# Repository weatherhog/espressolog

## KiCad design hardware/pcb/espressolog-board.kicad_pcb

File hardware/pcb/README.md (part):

# espressolog board — PCB (sense + drive)

One board to replace the hand-wired perfboard. The devkit sits in sockets,
both the sense dividers and the drive side are on it, and **the T-pieces are
on it too** (decided 2026-11-24). The perfboard keeps logging on the machine
until this board has passed its bench test.

**The source is `gen_schematic.py`, not the drawing.** The schematic is
label-based: every pin has a short stub and a net label, so the connectivity is
exactly the `part(...)` calls in the script. Edit the script and regenerate.
Do not edit the `.kicad_sch` by hand.

```bash
python3 gen_schematic.py --check
```

That writes `espressolog-board.kicad_sch` and the symbol library, then runs ERC
and exports the netlist from KiCad. It fails if any net differs from the script.
That proves the drawing matches the script. **It does not prove the script
matches the docs**: that needs a review against `docs/board-and-perfboard.md`
("Sense-side layout", "Drive-side layout") and `firmware/src/main.cpp`.

Needs KiCad 10 (`brew install --cask kicad`). Outputs go to `build/`, which is
not committed.

## The T-pieces are on the board

Each machine connector has two headers on the top edge:
- **IN** (J5, J4, J3, J2): side-entry, opening at the edge. The machine's
  **original harness plug** mates here.
- **OUT** (J25, J24, J23, J22): vertical, right behind its IN. A
  ready-made XH cable runs from here to the machine board's own header.
  **It must map pin 1 to pin 1.** Don't buy by the direction word: in
  同向 / 反向 ("same" / "reverse") listings, the pin-1-to-pin-1 cable is
  probably the one whose latches face OPPOSITE sides when laid flat. Two
  identical plugs on an uncrossed cable, both latches up, are mirrored
  (final review S1). Metering step 1 below decides, whatever the listing
  says.

**IN pin k is joined to OUT pin k by one straight track, for every line.** A
plug mates any XH header of its size the same way, so the machine sees its
own harness, conductor for conductor. The taps branch off the OUT pins. IN
and OUT of one connector are electrically interchangeable.

**A harness plug in the WRONG connector's header: closed for the harness
plugs, 2026-11-25.** The four have different pin counts (2, 3, 4, 5), and in
the paper test a smaller harness plug did not seat in a larger header. The
OUT cables are new parts and were not tried; the pairs are named on the silk
beside both headers.

**Operating consequence: the machine's switches, display and flowmeter all
run through this board. Without it, the machine runs only with the original
plugs back on its own headers.**

**The NTC plug stays on the machine's own J3 header for now** (pre-order
review S2). The J3 pass-through exists on the board, but an open or
resistive joint in it reads as a cold boiler, and with the tap unfitted it
delivers nothing. J3 is a 2-pin XH (confirmed 2026-11-24). The one planned
use before the tap is fitted is the measuring run in "The J3 NTC tap" below.
Before that run:
- find out, machine cold, what the machine does when J3 is pulled;
- meter the J3 rows as in "Before first fit" (pin 1 – pin 2 open, each pin
  open to TP1).

**The taps load the machine even when the ESP32 is off, and they cannot be
unplugged separately** (S12). With the devkit fitted but unpowered, its GPIO
protection diodes clamp the tap nodes, and the J5 bus high level is
calculated to drop from 4.20 V to about 3.5–3.8 V. That is at the floor the
display needs (`docs/phase-0-status.md`). **Measure it once**: machine on,
USB out, J25 pin 2 and pin 3 against TP1. Record the result here. If the
display misreads in that state, the cure is to pull the devkit or go back to
the original plugs.

**Pin map, by JST pin number** (pad 1 is the right-hand pin; the silk at the
top edge names each column, which is the same pin on IN and OUT).
**For J5 this is NOT `CLAUDE.md`'s numbering:** there, and in the display-bus
doc, pin 1 is `VSS` (the spoked pad) and pin 4 is `Disp-P4`. On this board
pad 1 is `Disp-P4` and pad 4 is `VSS`. Never clip a ground to "J5 pin 1" of
this board; ground is TP1.

| Conn | Pin 1 | Pin 2 | Pin 3 | Pin 4 | Pin 5 | Source |
|---|---|---|---|---|---|---|
| J5 / J25 | `Disp-P4` (P4) | `ESD4` clock (CK) | `ESD1` data (DA) | `VSS` (0V) | | pad 1 read off the plug (2026-11-24); the rest positional, `docs/machine-display-bus.md` |
| J4 / J24 | `#` | **`+`** (middle, green) | `T` | | | read off the machine-side plug, Lucas, 2026-11-24 (`J4_T_PIN = "3"` in `gen_schematic.py`) |
| J3 / J23 | NTC P1 | NTC P2 | | | | 109 kΩ between the two (2026-11-24); which is the divider node is unmeasured; the tap is DNP |
| J2 / J22 | pos 1 +5 V | Steam | 2Cup | 1Cup | Water | pad 1 read off the plug (2026-11-24); the rest positional (`CLAUDE.md`, J2 table) |

- **J4 `+` and J5 `Disp-P4` cross the board as isolated pass-through traces.**
  They have no pad but their own header pins, no test point, no via, no pour
  nearby, and keep 2 mm from everything of ours. Their own header's
  neighbouring pins sit at the machine's 2.5 mm pitch (0.8 mm gap, as in the
  machine's harness), and the pass-through tracks of those neighbours run
  1.45 mm from their pads (for `+` that includes J4's own ground, `T`).
  Nothing connects to them (the J4 `+` rule in `CLAUDE.md`).
- **The machine's ground (J5 `VSS`, J4 `T`) is our ground.** It passes
  straight through IN→OUT. J4 `T` ties to the devkit GND (J12 pin 1) by a
  hand-laid track, and J5 `VSS` joins that track through a via. The J2
  dividers' only reference is this ground.

## What the board carries

| Part | Note |
|---|---|
| J11 / J12 | devkit signal column (A) and opposite column (K), 1×22 female headers 25.4 mm apart, pin 1 (3V3) at the top. **Nothing on 5Vin.** Outline on the silkscreen |
| J2–J5 / J22–J25 | IN / OUT, above |
| R1–R16, C1–C3 | sense series legs and shunts. C1–C3 are DNP footprints for the candidate shunt caps (470 pF / 470 pF / 10 nF; **never 10 nF on ESD1/ESD4**) |
| R60–R68, C20–C22, U8 | **J3 NTC tap, ALL DNP** until J3 is measured (section "The J3 NTC tap" below). The machine's PID regulates on this NTC, so any load shifts the brew temperature, and a fault that reads cold keeps the heater on. Wash the flux off: leakage matters at 9.4 MΩ |
| U1, U2 | drive '221s, in sockets. **Crossed (pre-order review S1): U1 drives photoMOS 1 of each chain (U4, U6), U2 drives photoMOS 2 of each (U5, U7)**, so a fault in one package closes at most one device per chain. The perfboard doc has U1 = 1Cup, U2 = 2Cup. GPIOs, net names and firmware are the same either way |
| U3 | the PROPOSED gate '221. **Socket fitted, chip out, and R36 out with it** (R36 is marked DNP) |
| U4–U7 | AQY212EH in a DIP-8 footprint, with the chip at the pin-1 end of an uncut DIL08PZ (or soldered straight in). Pads 3–6 are not connected |
| Q1–Q4 + R40–R51 | LED-driver cells: 330 Ω, BC547B, 100 K, 8.2 K |
| JP1 (a1), JP2 (a2) | in series with the photoMOS outputs. **OPEN through Phase 0** (invariant 1) |
| JP3 (b) | LED supply. **OPEN until the bench test** |
| JP4 | selftest GPIO8–GPIO6. **Never fitted in service** |
| TP1 / TP2 | GND and 3V3 test loops for the scope and analyser |

**GPIO changes against the perfboard:** U1 pin 13's readback (1Cup
photoMOS 1) is on **GPIO11** (signal column position 17), and **GPIO1**
(opposite column position 4) is the NTC's ADC input (`30beb28`).

## Not settled. Check before ordering

- **J4: `+` is the MIDDLE pin; which outer pin is `T` is `J4_T_PIN`.** The
  first T-piece commit (`ee2795e`) took `docs/phase-0-status.md`'s "`T`
  (middle)" at its word and tied the machine's `+` to our GND. That doc was
  wrong, and Lucas read the plug. `T` is tied to our GND, so its side came
  from the plug, not a guess. `J4_T_PIN` and `J4_FLOW_PIN` are constants now
  and finish.py checks the pads against them: changing one stops the build
  until R3's position and the check are changed with it. That is the point.
- **Plug orientation: CONFIRMED 2026-11-24 for J4, J5 and J2.** Lucas read
  each machine-side plug from its wire end with the latches up (the latch
  faces up on a side-entry header, also confirmed), which mirrors left and
  right against the board frame:
  - J4: `+` (green) in the middle, `#` (black) on pad 1, `T` (yellow) on
    pad 3;
  - J5: `Disp-P4` on pad 1;
  - J2: the +5 V common on pad 1.

  The pre-power check below still confirms all three on the built board.
- **Capacitor lead pitch: checked in the paper test (2026-11-25).** The
  footprints are 5.0 mm. The 1 µF MKT and the 470 pF fit; the 100 nF discs
  in hand are narrower and get their legs splayed. The 10 nF was not tried.
- **BC547 footprint:** `TO-92_Inline_Wide`, with legs 2.54 mm apart like the
  perfboard's (the standard 1.27 mm one puts the collector–base pair close
  together). Pad 1 is C, and the review checked this against KiCad's stock
  BC547. A 2N3904 would go in reversed.
- **One GND net.** The perfboard kept separate drive (K29) and sense (K30)
  ground ties. Signal-column GND (A22, beside 5Vin) is deliberately left
  unused, as on the perfboard.
- **AQY212EH in an uncut DIP-8 footprint** where the board doc says DIP-4
  sockets: same netlist, and a chip pushed in at the wrong end lands on dead pads.
- **Box headroom above the top edge.** The OUT headers are vertical. A plug
  plus its cable bend needs ~20–25 mm above the board.
- **The open design items stay open**: the readback value (1 K proposed), the
  gate RC (470 K candidate), and whether the gate stays. They are on ordinary
  footprints, so values are chosen at soldering time. Dropping the gate is a
  bodge wire, GPIO38 to the arm net, not a solder jumper. The minimum-gap stage
  on U3's spare channel is not designed, so U3 channel 2 is tied off.

## The J3 NTC tap (all DNP, values not final)

J3 is the PID's own temperature sensor, so this is the one tap where a
mistake changes what the machine does to the boiler. Everything here is a
footprint; nothing is fitted until the measurements below exist.

**Measured so far (Lucas, 2026-11-24):** J3 is a 2-pin JST XH, and the
sensor reads **109 kΩ between its two wires**, plug off the machine board,
at what was presumably room temperature. That
fits a 100 kΩ NTC (B ≈ 3950 gives 109 kΩ at 23 °C), which would be roughly
6–9 kΩ at 95 °C. The B value, which pin is the divider node, the pull-up
and the node voltage are **not measured**.

**The circuit:**

| Part | Value | What it does |
|---|---|---|
| R60 **or** R61 | 4.7 MΩ, **fit ONE** | from the divider-node pin (R60 = pin 1, R61 = pin 2) to `NTC_MID`. Both fitted put 9.4 MΩ across the NTC |
| R64 | 4.7 MΩ | `NTC_MID` → `NTC_TAP`. Two parts in series, so one bridged or failed part still leaves 4.7 MΩ on the line |
| R62 | open | shunt to GND, only if the node turns out to sit above ~3 V (5 V referenced) |
| C20 | 10 nF | at the op-amp input |
| U8 half A | MCP6002 | unity follower (CMOS input, ~1 pA) |
| U8 half B, R66, R67 | Rf, Rg | follows half A. **Wire link in R66, R67 empty = unity** (the parked default). R66/R67 fitted = gain 1 + R66/R67, for a node that sits low when hot. **Whenever U8 is fitted, R66 is fitted** (link or Rf): without it half B runs open-loop |
| R63 **or** R68 | 1 kΩ, **fit ONE** | R63 from the follower, R68 from the gain stage, into `NTC_ADC` |
| C21, C22 | 100 nF | on `NTC_ADC` (GPIO1, ADC1), and U8's supply |

**What it costs the machine.** In normal running the follower draws
nothing, so the load is leakage only. The worst case is the tap node held
at a rail, and that is also the everyday case of **machine on, logger
off**: U8's input clamps to its dead supply. Then 9.4 MΩ sits across the
node. Against ≤ 9 kΩ at brew temperature that is under 0.1 % of the
reading, about 0.03 °C; against 109 kΩ cold it is ~1.2 %, about 0.3 °C.
**Which way it reads is not known yet:** slightly hot (the direction that
heats less) if the NTC is the leg to ground, slightly cold by the same
amount if it is the leg to the supply. Step 1 below settles it.

**Still to measure, and none of it needs a hand-built T-piece:**
1. **Now, machine off and unplugged:** each pin of the machine board's J3
   header to ground (J5's spoked pad), in Ω. One pin near 0 Ω means that pin
   is ground and the other is the node. (Back-probing J4's header gave no
   reading before; if J3 does the same, skip it, step 2 answers it too.)
2. **With this board, tap unfitted** (after the two checks under "The NTC
   plug stays on the machine" above): J3 through IN → OUT like the other
   three, **with the J5 or J4 OUT cable on the machine too** (TP1 is only
   the machine's ground through one of those). The board is the T-piece.
   Meter J23 pin 1 and pin 2 against TP1 in
   DC volts, cold and at setpoint, and note whether the reading is steady (a
   pulsed excitation would not be). A 10 MΩ meter loads the node as much as
   the tap will.

Those readings choose R60 or R61, whether R62 is needed, and the gain
(largest that keeps the hot-end voltage under ~2.5 V at GPIO1). **Running
J3 through the board is itself the risk this section is about**: an open
pass-through reads cold and the heater stays on. Seat both plugs fully and
watch the display on the first heat-up.

Firmware reads nothing on GPIO1 yet. When it does, it stores raw
millivolts (invariant 3) and the conversion lives in analysis.

## Before first fit: meter it

Board unpowered, devkit out, DNP parts unfitted, the NTC plug left on the
machine.

0. **The jumpers are open.** Each of JP1, JP2, JP3 and JP4 reads open across
   its two posts. J22 pin 1 reads open to U4 pad 8 and to U6 pad 8. The posts
   are 0.84 mm apart and hand-soldered, and a bridged JP1 or JP2 is invisible
   from the connectors. Invariant 1 rests on this.

1. **Each OUT cable, on this board.** Plug its two ends into that
   connector's own IN and OUT headers (no harness, no machine).
   - **Correct cable:** pin 1 ↔ pin 1. Each line only loops back to itself,
     so no two different pins are joined.
   - **Mirrored cable:** pin k ↔ pin n+1−k, so pin 1 is shorted to pin n.

   No cavity numbering is needed. Meter on the IN header's solder side:
   - J5: pin 1 – pin 4 must read open (mirrored: `Disp-P4` on GND), and
     pin 2 – pin 3 must read ~49 kΩ (mirrored: ~0);
   - J4: pin 1 – pin 3 must read ~320 kΩ (mirrored: `#` on GND, the `E01`
     class);
   - J3: pin 1 – pin 2 must read open;
   - J2: pin 1 – pin 5 must read open, and pin 2 – pin 4 ~740 kΩ.

   **Any ~0 Ω reading means a mirrored cable, which must not be used.**

   This step finds a mirrored cable and nothing else: an unseated cable or a
   broken conductor reads the same as a good one. So, **for every conductor**:
   one end in the OUT header, probe each contact of the free plug to the
   same pin of the IN header, ~0 Ω.
2. **Board pass-through.** IN pin k reads ~0 Ω to OUT pin k, and **not
   ~0 Ω** to any other pin of either header. The readings between different
   pins are the board's own dividers, not opens:
   - J5: pin 2–3 ≈ 49 kΩ, pin 2 or 3 to pin 4 ≈ 24.6 kΩ, pin 1 open to all;
   - J4: pin 1–3 ≈ 320 kΩ, pin 2 open to all;
   - J2: any two of pins 2–5 ≈ 740 kΩ, pin 1 open to all;
   - J3: open.

   A ~0 Ω reading is a solder bridge.
3. **The isolated lines.** J24 pin 2 (`+`, the middle one) and J25 pin 1
   (`Disp-P4`) read open to every other pin, to TP1 (GND) and to TP2 (3V3).
   J23 pins 1 and 2 read open to everything.
4. **Ground.** J25 pin 4 and the J24 `T` pin read ~0 Ω to TP1, and **J24
   pin 2 does NOT** (that reading is the `ee2795e` short). No J2 pin reads
   ~0 to TP1.
5. **Taps by value**, header pin to devkit socket position:
   - 8.2 kΩ: J25 pin 3 → A5 and J25 pin 2 → A4;
   - 100 kΩ: the J24 `#` pin → A6;
   - 150 kΩ: J22 pins 5, 4, 3, 2 → A10, A7, A8, A9 (the 100 K and 150 K bags
     look alike).
   - Then the shunts, socket position to TP1: A4 and A5 16.4 kΩ, A6–A10
     220 kΩ.
6. **At the machine**, machine off and unplugged from the mains, OUT cables
   to the machine board, harness plugs NOT on the IN headers:
   - TP1 reads ~0 Ω to J5's spoked pad (`VSS`) and to J4's `T`;
   - J24 pin 2 reads ~0 Ω to the machine's J4 `+`, and **not ~0 Ω to TP1**.
     It is never "open" there: the machine's own path `+` → 10 k → `#` →
     147 k → `T` (with our 320 k beside it) reads about 110 kΩ, and the
     unpowered 5 V rail can pull that lower. The value to expect is the
     `+`–`T` reading taken on the machine's own J4 plug (below); a reading
     near **10 kΩ** points at a mirrored J4 cable, and anything under
     ~1 kΩ, down to ~0 Ω, means `+` is on or near ground: stop either way;
   - the J24 `#` pin reads ~0 Ω to `#`;
   - J25 pin 1 reads ~0 Ω to J5's square pad (`Disp-P4`);
   - J22 pin 1 reads ~0 Ω to the machine's J2 common, the pin in every
     lever's continuity pair.

   This confirms the J5, J4 and J2 orientation on the real machine.

   **If the machine board's pins can't be probed** (back-probing J4 gave no
   reading before), there is a J4 check that needs no access to them, derived
   from the 2026-10-04 readings and not yet tried in this form: with the J24
   cable on the unpowered machine and no harness plug, **J24 pin 1 – pin 2
   reads ≈ 10 kΩ** (the machine's pull-up from `#` to `+`), and TP1 – J24
   pin 2 does not. With a mirrored J4 cable both read ≈ 10 kΩ (with J5's
   cable on, `#` is then on `T` through our ground).
   **This only discriminates if the machine's unpowered 5 V rail reads well
   above 10 kΩ, and nobody has measured it.** Meter `+` to `T` once on the
   machine's own J4 plug (machine off, no board attached) before relying on
   it. If that reads near 10 kΩ the two readings look alike and this check
   says nothing.
7. Only then do the harness plugs go on the IN headers (not the NTC's).

**`selftest`:** "unplug J4 first" now means the **J24 OUT cable**. Pulling
only the harness plug leaves GPIO8 on the machine's `#` node through 100 K.

## Building the board

Placement, routing and finishing are scripts too. Each runs with KiCad's
Python (`KPY=/Applications/KiCad/KiCad.app/Contents/Frameworks/Python.framework/Versions/3.9/bin/python3`):

```bash
python3 gen_schematic.py --check   # schematic, ERC, netlist round-trip
$KPY gen_pcb.py                    # placement + the machine nets as locked tracks
$KPY route.py                      # Freerouting the rest, headless (Java 21+, jar in ~/.local/share/freerouting)
$KPY route.py --keep               # second pass: keeps the routes, completes what is still open
$KPY finish.py                     # GND pours (both layers), keep-outs, labels, refs
```

`route.py` can be re-run on a routed board. It strips everything except the
locked tracks in a separate process, then routes. **One pass does not always
finish**: with the tight rules the router can leave a connection open, and
the result varies from run to run. `route.py --keep` routes again on top of
what is there. Repeat it until DRC after `finish.py` shows 0 unconnected.
While routing, the router is kept out of the J5/J4 header block, out of the
corridor between the J3 rows, 1 mm off every board edge, and **out from
under every hand-laid machine track** (a strip on the opposite layer: no
clearance rule sees opposite layers, and one re-route on 2026-11-24 took a
drive net between the J2 rows under all five lever pass-throughs).

**A router run is not reproducible, and it can leave connections open.**
`route.py` prints `open connections: N`; run `route.py --keep` until it is 0,
and if two or three passes do not close it, start again from `gen_pcb.py`
(the next fresh run usually does). The pipeline no longer finishes a bad
board quietly:
- `route.py` deletes `build/routed.kicad_pcb` and the old router session
  before it starts, and stops if Freerouting fails;
- `finish.py` starts from `build/routed.kicad_pcb` and **stops before
  saving** unless: every pad is on the net `gen_schematic.py` gives it; the
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
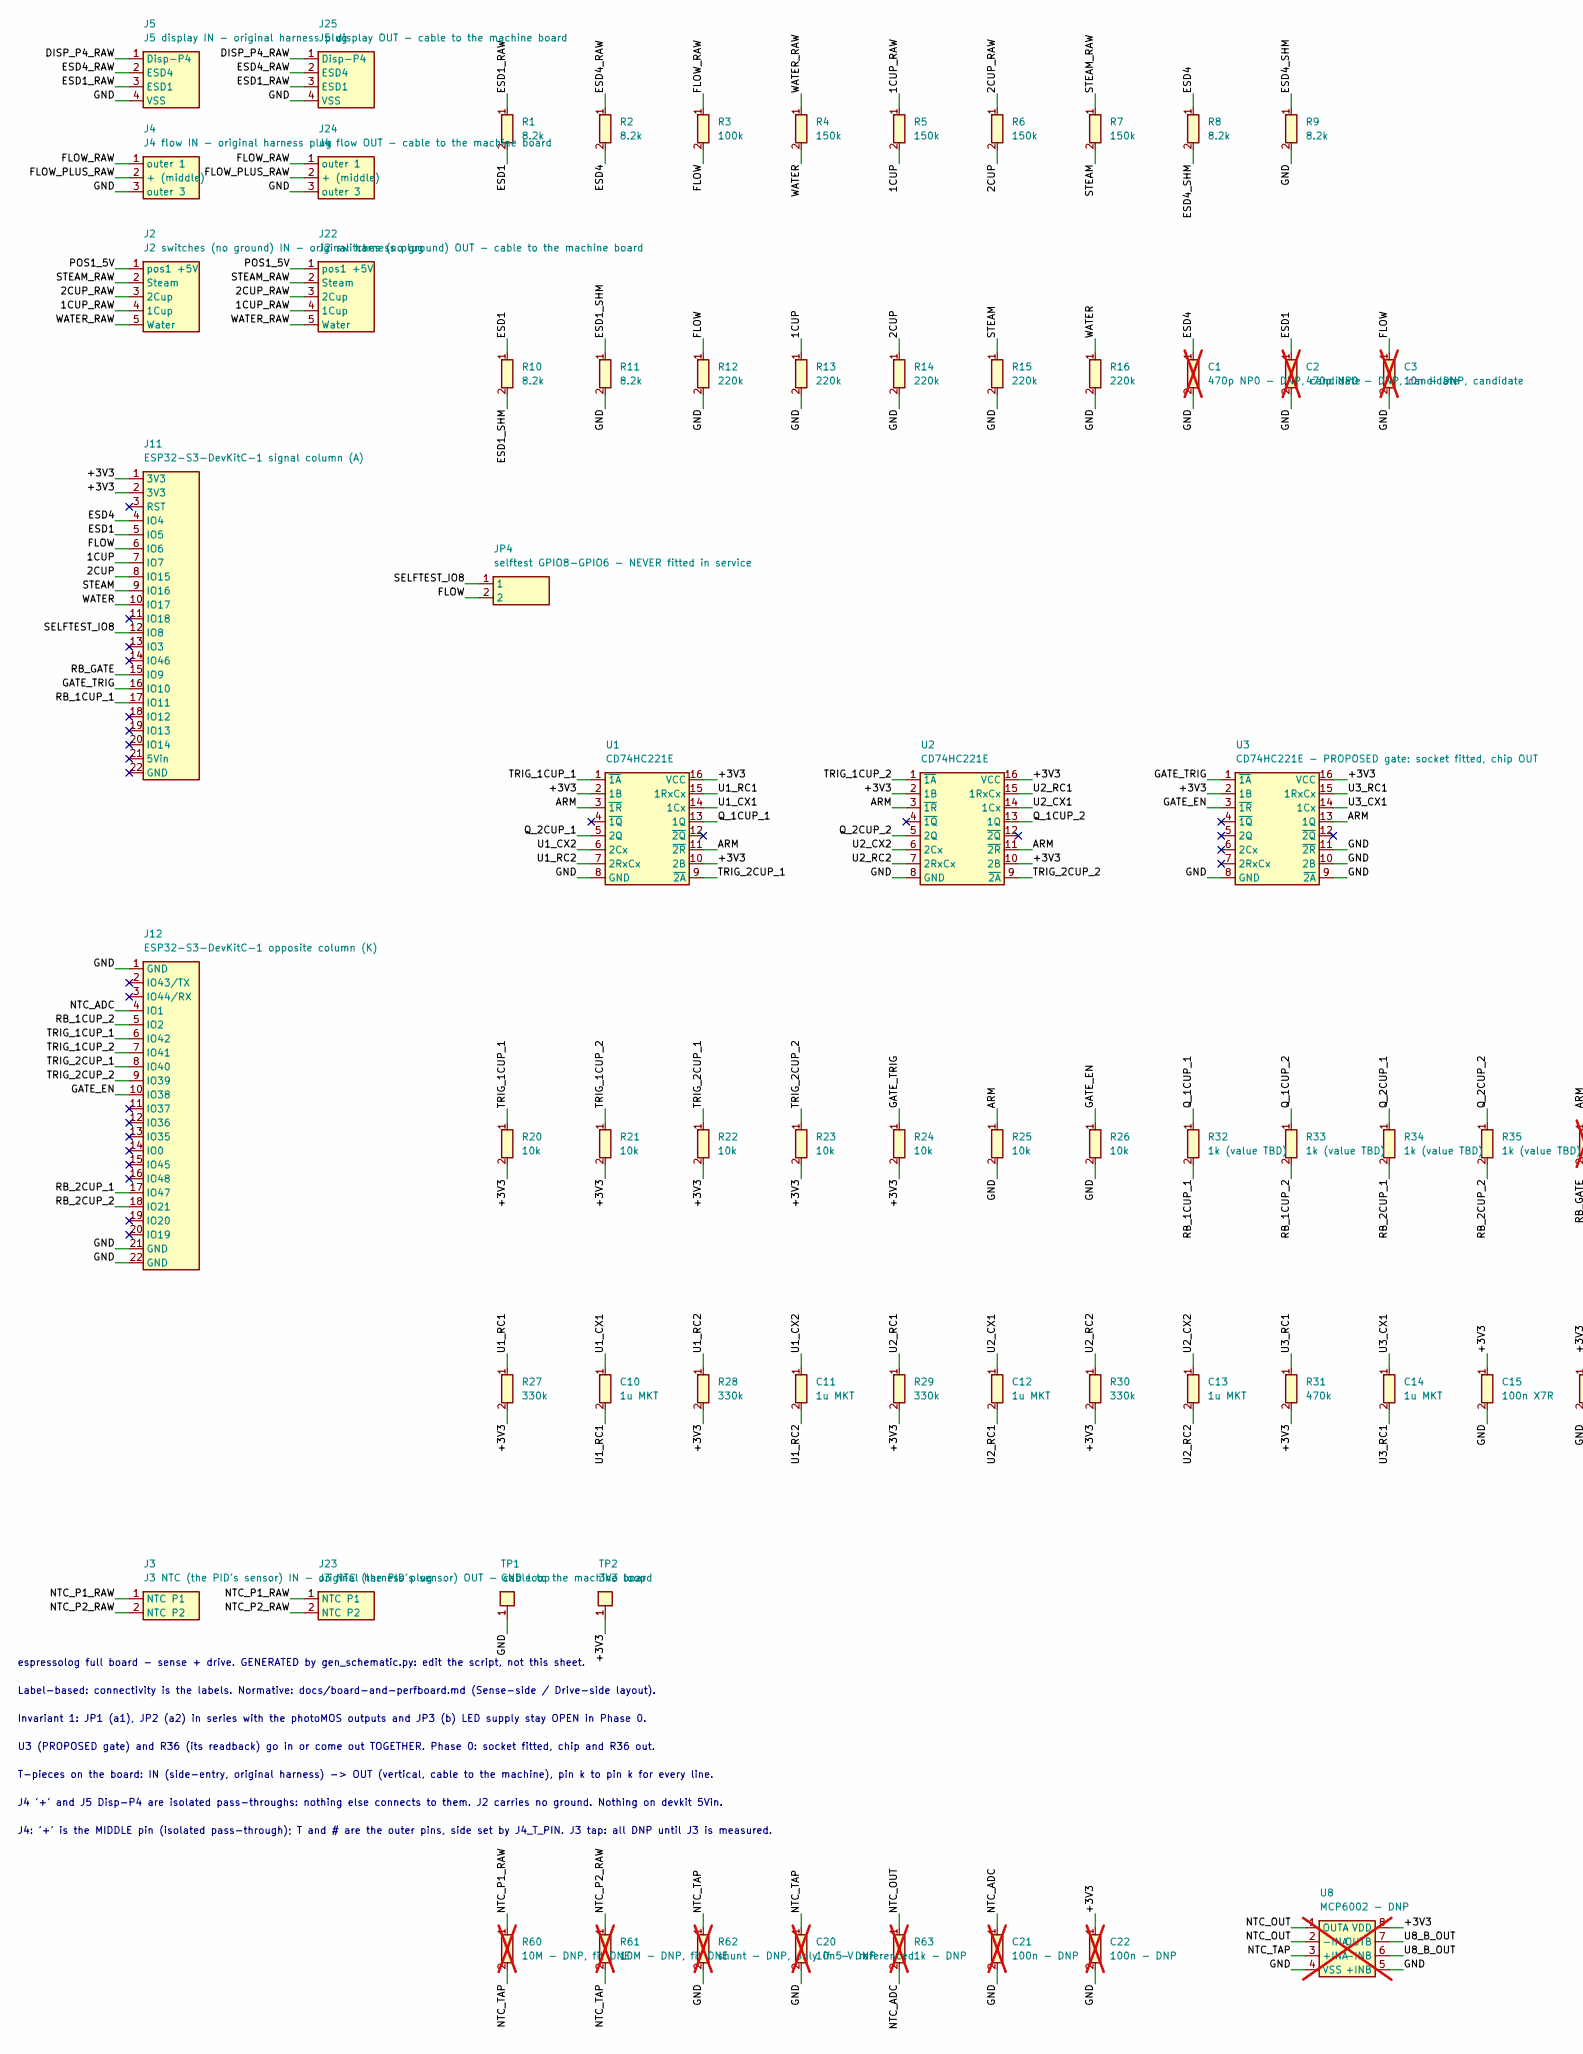
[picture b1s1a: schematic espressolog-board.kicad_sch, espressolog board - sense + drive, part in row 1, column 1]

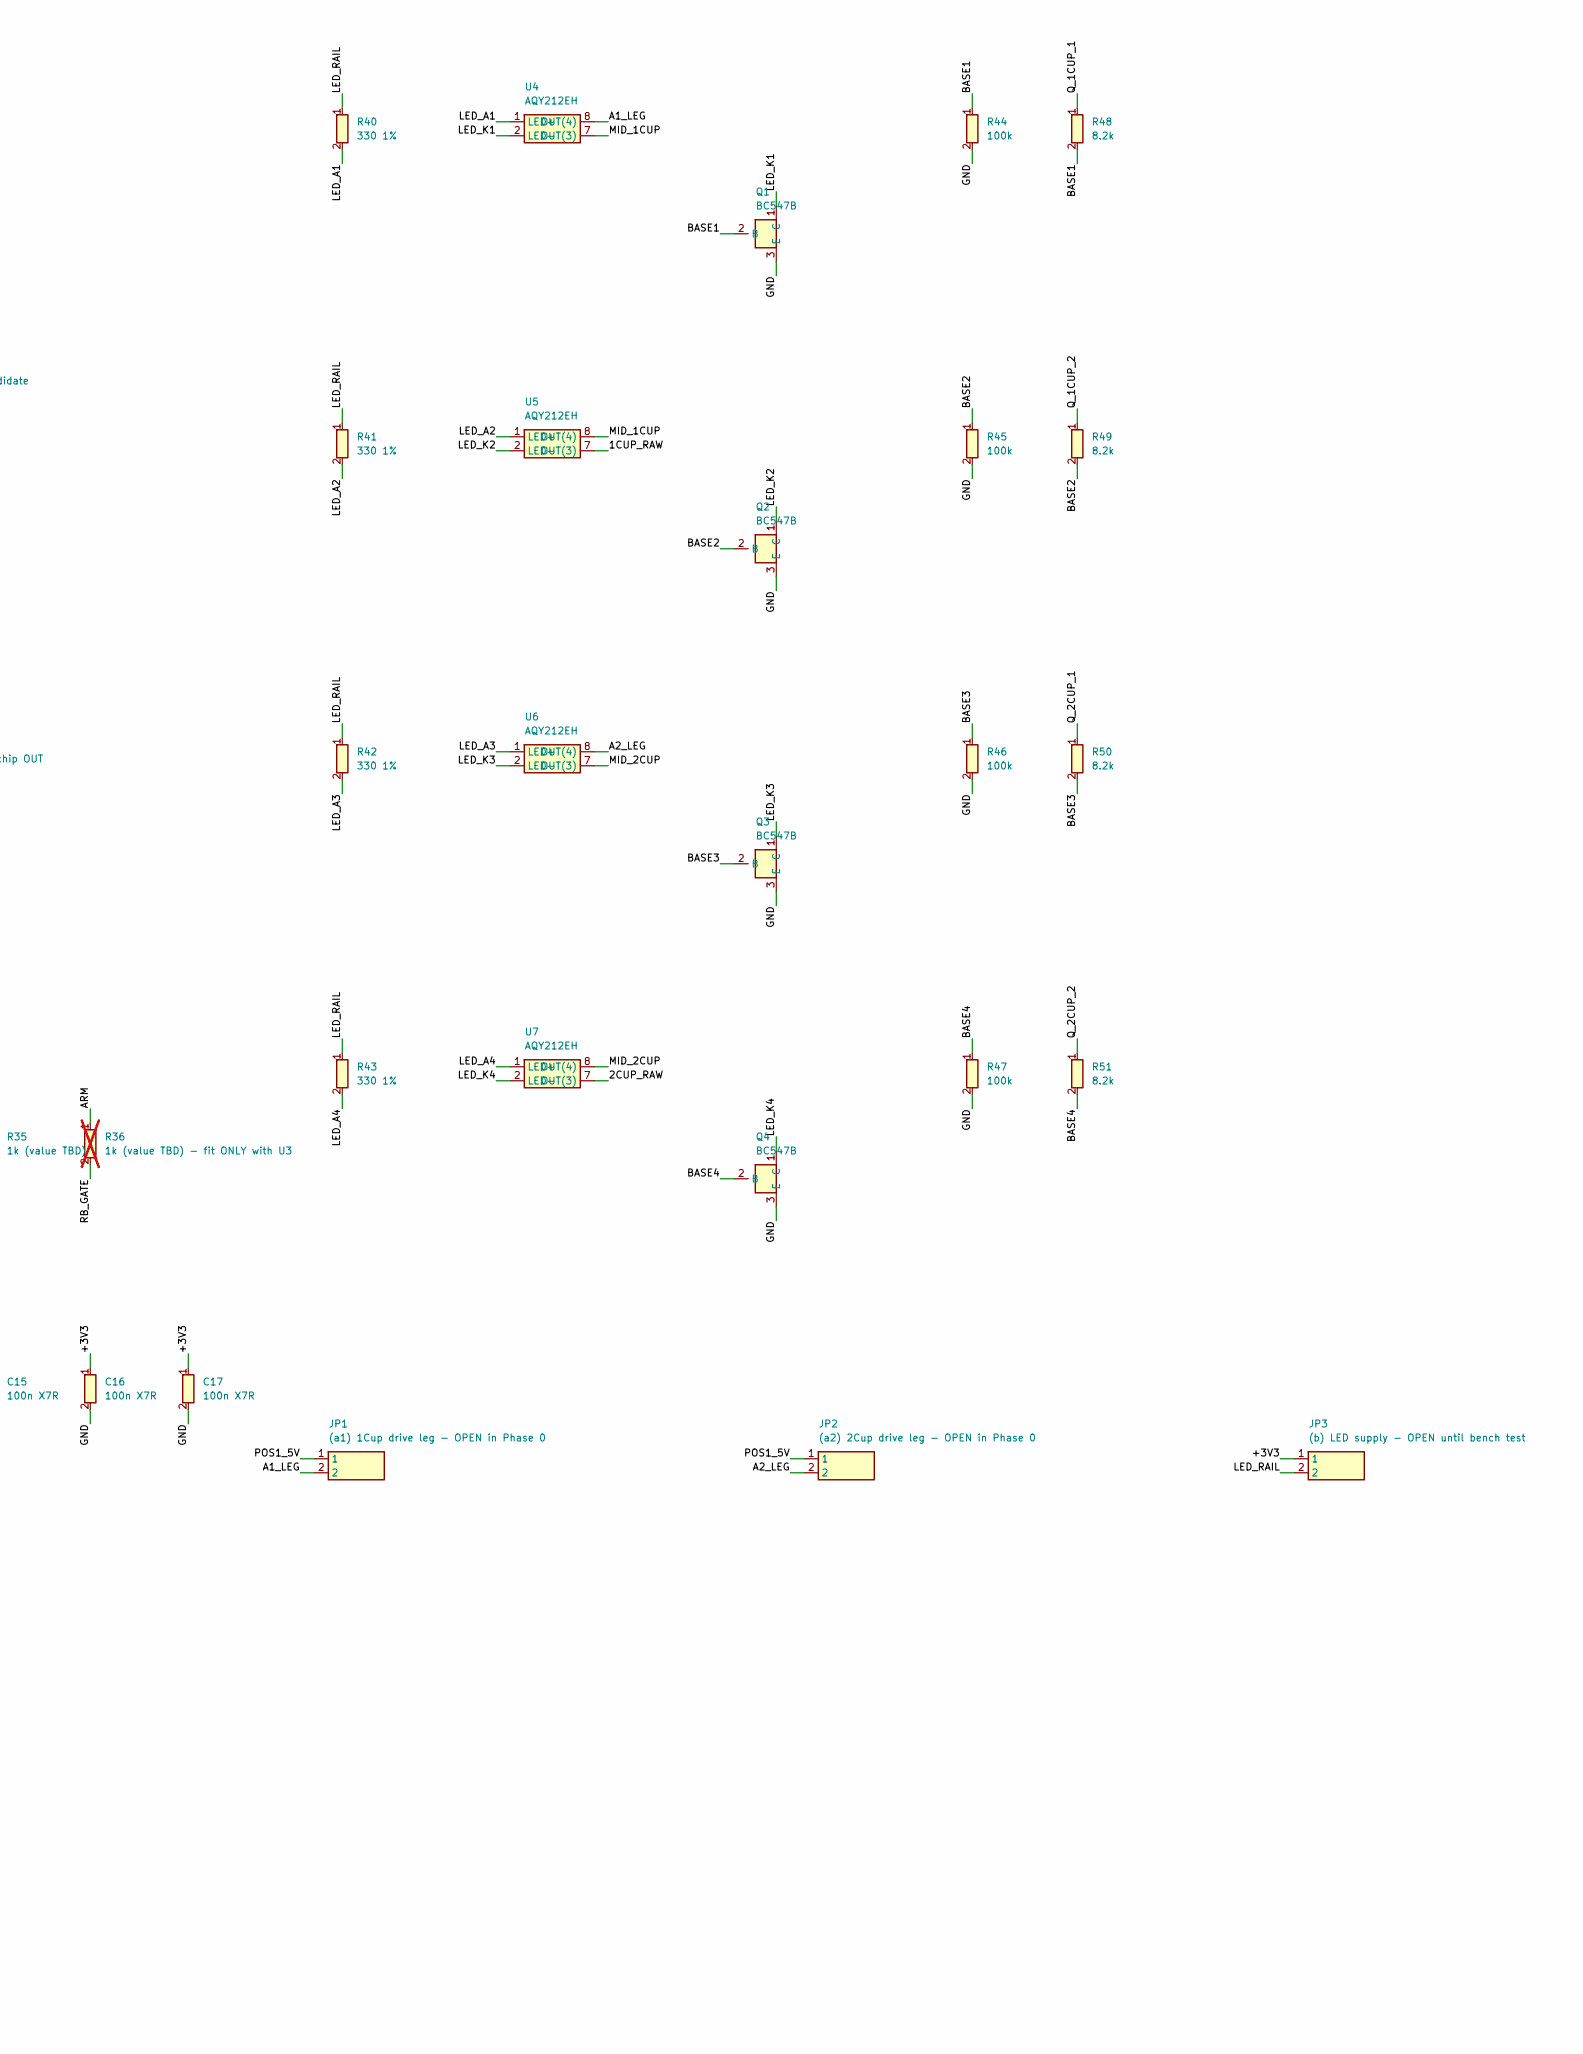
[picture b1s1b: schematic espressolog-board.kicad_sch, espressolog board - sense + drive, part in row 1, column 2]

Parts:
C1, C2: 470p NP0 - DNP, candidate; C_Disc_D5.0mm_W2.5mm_P5.00mm; not fitted
C3: 10n - DNP, candidate; C_Disc_D5.0mm_W2.5mm_P5.00mm; not fitted
C10, C11, C12, C13, C14: 1u MKT; C_Rect_L7.2mm_W5.5mm_P5.00mm_FKS2_FKP2_MKS2_MKP2
C15, C16, C17: 100n X7R; C_Disc_D5.0mm_W2.5mm_P5.00mm
C20: 10n - DNP; C_Disc_D5.0mm_W2.5mm_P5.00mm; not fitted
C21, C22: 100n - DNP; C_Disc_D5.0mm_W2.5mm_P5.00mm; not fitted
J2: J2 switches (no ground) IN - original harness plug; JST_XH_S5B-XH-A_1x05_P2.50mm_Horizontal
J3: J3 NTC (the PID's sensor) IN - original harness p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; JST_XH_S2B-XH-A_1x02_P2.50mm_Horizontal
J4: J4 flow IN - original harness plug; JST_XH_S3B-XH-A_1x03_P2.50mm_Horizontal
J5: J5 display IN - original harness plug; JST_XH_S4B-XH-A_1x04_P2.50mm_Horizontal
J11: ESP32-S3-DevKitC-1 signal column (A); PinSocket_1x22_P2.54mm_Vertical
J12: ESP32-S3-DevKitC-1 opposite column (K); PinSocket_1x22_P2.54mm_Vertical
J22: J2 switches (no ground) OUT - cable to the machin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; JST_XH_B5B-XH-A_1x05_P2.50mm_Vertical
J23: J3 NTC (the PID's sensor) OUT - cable to the mach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; JST_XH_B2B-XH-A_1x02_P2.50mm_Vertical
J24: J4 flow OUT - cable to the machine board; JST_XH_B3B-XH-A_1x03_P2.50mm_Vertical
J25: J5 display OUT - cable to the machine board; JST_XH_B4B-XH-A_1x04_P2.50mm_Vertical
JP1: (a1) 1Cup drive leg - OPEN in Phase 0; PinHeader_1x02_P2.54mm_Vertical
JP2: (a2) 2Cup drive leg - OPEN in Phase 0; PinHeader_1x02_P2.54mm_Vertical
JP3: (b) LED supply - OPEN until bench test; PinHeader_1x02_P2.54mm_Vertical
JP4: selftest GPIO8-GPIO6 - NEVER fitted in service; PinHeader_1x02_P2.54mm_Vertical
Q1, Q2, Q3, Q4: BC547B; TO-92_Inline_Wide
R1, R2, R8, R9, R10, R11: 8.2k; R_Axial_DIN0207_L6.3mm_D2.5mm_P10.16mm_Horizontal
R3: 100k; R_Axial_DIN0207_L6.3mm_D2.5mm_P10.16mm_Horizontal
R4, R5, R6, R7: 150k; R_Axial_DIN0207_L6.3mm_D2.5mm_P7.62mm_Horizontal
R12, R13, R14, R15, R16: 220k; R_Axial_DIN0207_L6.3mm_D2.5mm_P10.16mm_Horizontal
R20, R21, R22, R23, R24, R25, R26: 10k; R_Axial_DIN0207_L6.3mm_D2.5mm_P2.54mm_Vertical
R27, R28, R29, R30: 330k; R_Axial_DIN0207_L6.3mm_D2.5mm_P2.54mm_Vertical
R31: 470k; R_Axial_DIN0207_L6.3mm_D2.5mm_P2.54mm_Vertical
R32, R33, R34, R35: 1k (value TBD); R_Axial_DIN0207_L6.3mm_D2.5mm_P2.54mm_Vertical
R36: 1k (value TBD) - fit ONLY with U3; R_Axial_DIN0207_L6.3mm_D2.5mm_P2.54mm_Vertical; not fitted
R40, R41, R42, R43: 330 1%; R_Axial_DIN0207_L6.3mm_D2.5mm_P2.54mm_Vertical
R44, R45, R46, R47: 100k; R_Axial_DIN0207_L6.3mm_D2.5mm_P2.54mm_Vertical
R48, R49, R50, R51: 8.2k; R_Axial_DIN0207_L6.3mm_D2.5mm_P2.54mm_Vertical
R60, R61: 10M - DNP, fit ONE; R_Axial_DIN0207_L6.3mm_D2.5mm_P5.08mm_Vertical; not fitted
R62: shunt - DNP, only if 5 V referenced; R_Axial_DIN0207_L6.3mm_D2.5mm_P2.54mm_Vertical; not fitted
R63: 1k - DNP; R_Axial_DIN0207_L6.3mm_D2.5mm_P2.54mm_Vertical; not fitted
TP1: GND loop; TestPoint_Loop_D2.50mm_Drill1.0mm
TP2: 3V3 loop; TestPoint_Loop_D2.50mm_Drill1.0mm
U1, U2: CD74HC221E; DIP-16_W7.62mm_Socket
U3: CD74HC221E - PROPOSED gate: socket fitted, chip O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; DIP-16_W7.62mm_Socket
U4, U5, U6, U7: AQY212EH; DIP-8_W7.62mm_Socket
U8: MCP6002 - DNP; DIP-8_W7.62mm; not fitted

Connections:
1CUP: J11.7 (IO7), R5.2, R13.1
1CUP_RAW: J2.4 (1Cup), J22.4 (1Cup), R5.1, U5.7 (OUT(3))
2CUP: J11.8 (IO15), R6.2, R14.1
2CUP_RAW: J2.3 (2Cup), J22.3 (2Cup), R6.1, U7.7 (OUT(3))
+3V3: C15.1, C16.1, C17.1, C22.1, J11.1 (3V3), J11.2 (3V3), JP3.1, R20.2, R21.2, R22.2, R23.2, R24.2, R27.2, R28.2, R29.2, R30.2, R31.2, TP2.1, U1.2 (1B), U1.10 (2B), U1.16 (VCC), U2.2 (1B), U2.10 (2B), U2.16 (VCC), U3.2 (1B), U3.16 (VCC), U8.8 (VDD)
A1_LEG: JP1.2, U4.8 (OUT(4))
A2_LEG: JP2.2, U6.8 (OUT(4))
ARM: R25.1, R36.1, U1.3 (~1R), U1.11 (~2R), U2.3 (~1R), U2.11 (~2R), U3.13 (1Q)
BASE1: Q1.2 (B), R44.1, R48.2
BASE2: Q2.2 (B), R45.1, R49.2
BASE3: Q3.2 (B), R46.1, R50.2
BASE4: Q4.2 (B), R47.1, R51.2
DISP_P4_RAW: J5.1 (Disp-P4), J25.1 (Disp-P4)
ESD1: C2.1, J11.5 (IO5), R1.2, R10.1
ESD1_RAW: J5.3 (ESD1), J25.3 (ESD1), R1.1
ESD1_SHM: R10.2, R11.1
ESD4: C1.1, J11.4 (IO4), R2.2, R8.1
ESD4_RAW: J5.2 (ESD4), J25.2 (ESD4), R2.1
ESD4_SHM: R8.2, R9.1
FLOW: C3.1, J11.6 (IO6), JP4.2, R3.2, R12.1
FLOW_PLUS_RAW: J4.2 (+ (middle)), J24.2 (+ (middle))
FLOW_RAW: J4.1 (outer 1), J24.1 (outer 1), R3.1
GATE_EN: J12.10 (IO38), R26.1, U3.3 (~1R)
GATE_TRIG: J11.16 (IO10), R24.1, U3.1 (~1A)
LED_A1: R40.2, U4.1 (LED+)
LED_A2: R41.2, U5.1 (LED+)
LED_A3: R42.2, U6.1 (LED+)
LED_A4: R43.2, U7.1 (LED+)
LED_K1: Q1.1 (C), U4.2 (LED-)
LED_K2: Q2.1 (C), U5.2 (LED-)
LED_K3: Q3.1 (C), U6.2 (LED-)
LED_K4: Q4.1 (C), U7.2 (LED-)
LED_RAIL: JP3.2, R40.1, R41.1, R42.1, R43.1
MID_1CUP: U4.7 (OUT(3)), U5.8 (OUT(4))
MID_2CUP: U6.7 (OUT(3)), U7.8 (OUT(4))
NTC_ADC: C21.1, J12.4 (IO1), R63.2; also elsewhere on the board
NTC_P1_RAW: J3.1 (NTC P1), J23.1 (NTC P1), R60.1
NTC_P2_RAW: J3.2 (NTC P2), J23.2 (NTC P2), R61.1
POS1_5V: J2.1 (pos1 +5V), J22.1 (pos1 +5V), JP1.1, JP2.1
Q_1CUP_1: R32.1, R48.1, U1.13 (1Q)
Q_1CUP_2: R33.1, R49.1, U2.13 (1Q)
Q_2CUP_1: R34.1, R50.1, U1.5 (2Q)
Q_2CUP_2: R35.1, R51.1, U2.5 (2Q)
RB_1CUP_1: J11.17 (IO11), R32.2
RB_1CUP_2: J12.5 (IO2), R33.2
RB_2CUP_1: J12.17 (IO47), R34.2
RB_2CUP_2: J12.18 (IO21), R35.2
RB_GATE: J11.15 (IO9), R36.2
SELFTEST_IO8: J11.12 (IO8), JP4.1
STEAM: J11.9 (IO16), R7.2, R15.1
STEAM_RAW: J2.2 (Steam), J22.2 (Steam), R7.1
TRIG_1CUP_1: J12.6 (IO42), R20.1, U1.1 (~1A)
TRIG_1CUP_2: J12.7 (IO41), R21.1, U2.1 (~1A)
TRIG_2CUP_1: J12.8 (IO40), R22.1, U1.9 (~2A)
TRIG_2CUP_2: J12.9 (IO39), R23.1, U2.9 (~2A)
U1_CX1: C10.1, U1.14 (1Cx)
U1_CX2: C11.1, U1.6 (2Cx)
U1_RC1: C10.2, R27.1, U1.15 (1RxCx)
U1_RC2: C11.2, R28.1, U1.7 (2RxCx)
U2_CX1: C12.1, U2.14 (1Cx)
U2_CX2: C13.1, U2.6 (2Cx)
U2_RC1: C12.2, R29.1, U2.15 (1RxCx)
U2_RC2: C13.2, R30.1, U2.7 (2RxCx)
U3_CX1: C14.1, U3.14 (1Cx)
U3_RC1: C14.2, R31.1, U3.15 (1RxCx)
WATER: J11.10 (IO17), R4.2, R16.1
WATER_RAW: J2.5 (Water), J22.5 (Water), R4.1

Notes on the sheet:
espressolog full board - sense + drive. GENERATED by gen_schematic.py: edit the script, not this sheet.
Label-based: connectivity is the labels. Normative: docs/board-and-perfboard.md (Sense-side / Drive-side layout).
Invariant 1: JP1 (a1), JP2 (a2) in series with the photoMOS outputs and JP3 (b) LED supply stay OPEN in Phase 0.
U3 (PROPOSED gate) and R36 (its readback) go in or come out TOGETHER. Phase 0: socket fitted, chip and R36 out.
T-pieces on the board: IN (side-entry, original harness) -> OUT (vertical, cable to the machine), pin k to pin k for every line.
J4 '+' and J5 Disp-P4 are isolated pass-throughs: nothing else connects to them. J2 carries no ground. Nothing on devkit 5Vin.
J4: '+' is the MIDDLE pin (isolated pass-through); T and # are the outer pins, side set by J4_T_PIN. J3 tap: all DNP until J3 is measured.

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
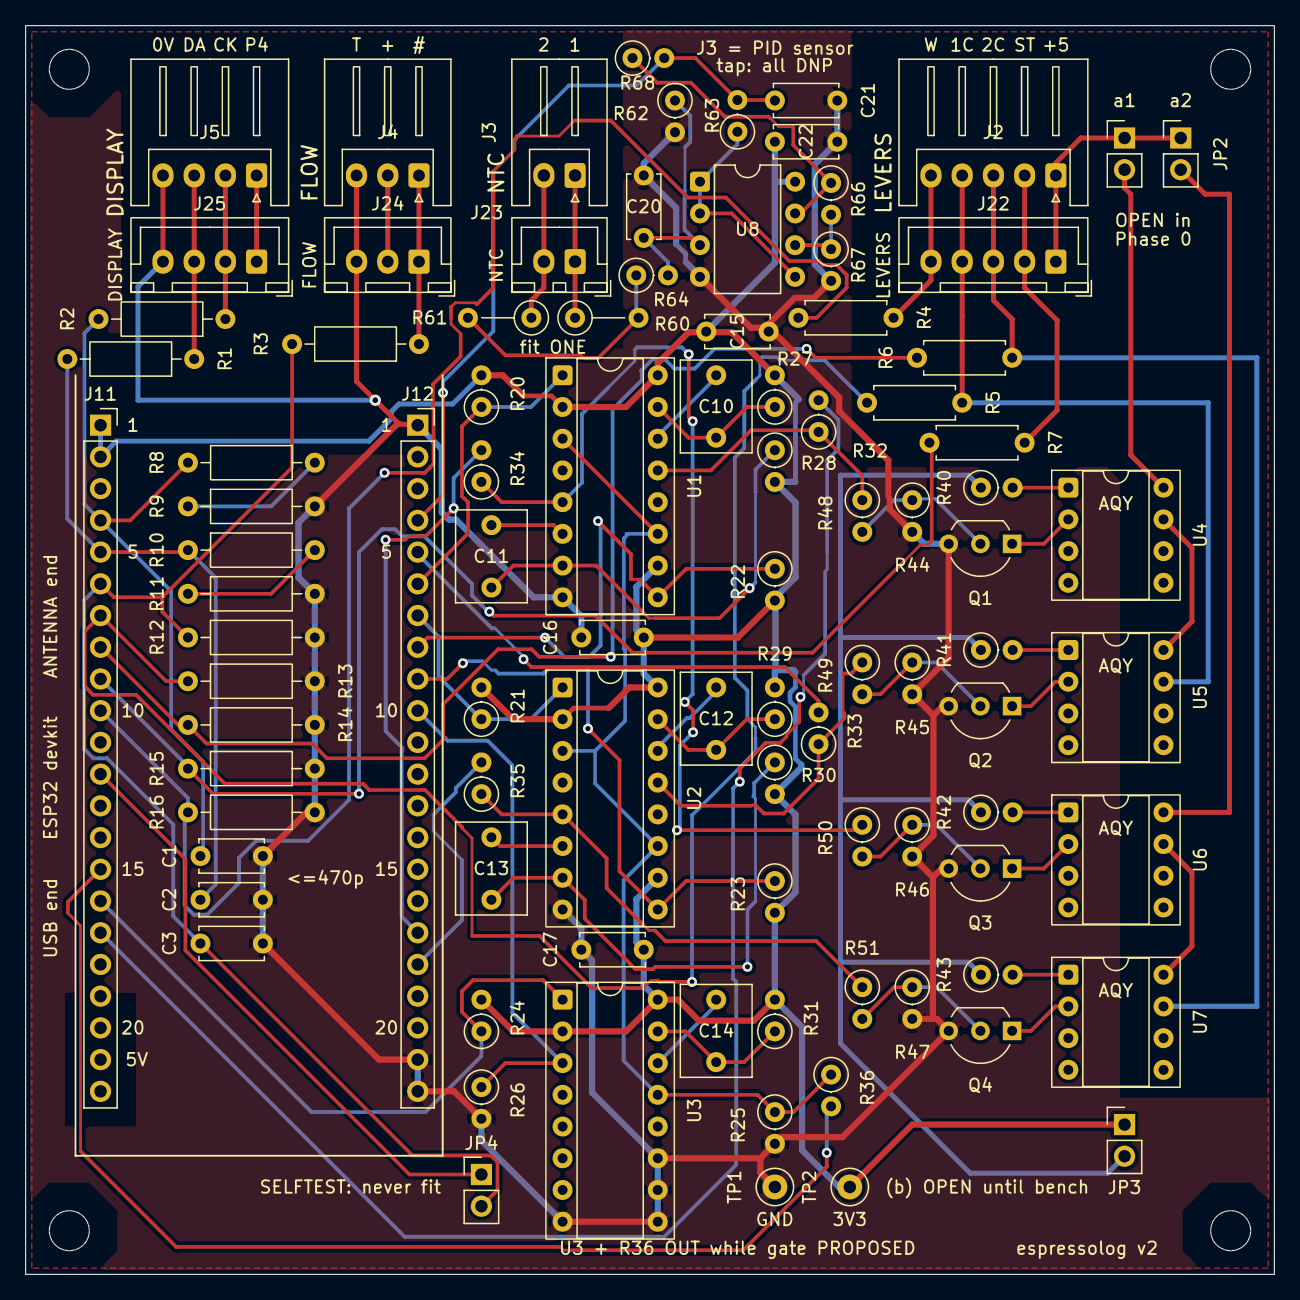
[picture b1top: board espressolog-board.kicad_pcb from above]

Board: 2 copper layers, 100.0 x 100.0 mm, 99 parts (0 on the bottom side), 73 nets.

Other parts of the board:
H1, H2, H3, H4: MountingHole_3.2mm_M3
R64: 4.7M - DNP; R_Axial_DIN0207_L6.3mm_D2.5mm_P2.54mm_Vertical
R66: Rf - DNP: wire link = unity; R_Axial_DIN0207_L6.3mm_D2.5mm_P2.54mm_Vertical
R67: Rg - DNP, gain only; R_Axial_DIN0207_L6.3mm_D2.5mm_P2.54mm_Vertical
R68: 1k - DNP, fit ONE of R63/R68; R_Axial_DIN0207_L6.3mm_D2.5mm_P2.54mm_Vertical

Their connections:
NTC_ADC: R68.2; also elsewhere on the board

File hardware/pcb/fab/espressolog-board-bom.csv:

"Reference","Value","Footprint","DNP","QUANTITY"
"C1,C2","470p NP0 - DNP, candidate","Capacitor_THT:C_Disc_D5.0mm_W2.5mm_P5.00mm","DNP","2"
"C3","10n - DNP, candidate","Capacitor_THT:C_Disc_D5.0mm_W2.5mm_P5.00mm","DNP","1"
"C10-C14","1u MKT","Capacitor_THT:C_Rect_L7.2mm_W5.5mm_P5.00mm_FKS2_FKP2_MKS2_MKP2","","5"
"C15-C17","100n X7R","Capacitor_THT:C_Disc_D5.0mm_W2.5mm_P5.00mm","","3"
"C20","10n - DNP","Capacitor_THT:C_Disc_D5.0mm_W2.5mm_P5.00mm","DNP","1"
"C21,C22","100n - DNP","Capacitor_THT:C_Disc_D5.0mm_W2.5mm_P5.00mm","DNP","2"
"J2","J2 switches (no ground) IN - original harness plug","Connector_JST:JST_XH_S5B-XH-A_1x05_P2.50mm_Horizontal","","1"
"J3","J3 NTC (the PID's sensor) IN - original harness plug","Connector_JST:JST_XH_S2B-XH-A_1x02_P2.50mm_Horizontal","","1"
"J4","J4 flow IN - original harness plug","Connector_JST:JST_XH_S3B-XH-A_1x03_P2.50mm_Horizontal","","1"
"J5","J5 display IN - original harness plug","Connector_JST:JST_XH_S4B-XH-A_1x04_P2.50mm_Horizontal","","1"
"J11","ESP32-S3-DevKitC-1 signal column (A)","Connector_PinSocket_2.54mm:PinSocket_1x22_P2.54mm_Vertical","","1"
"J12","ESP32-S3-DevKitC-1 opposite column (K)","Connector_PinSocket_2.54mm:PinSocket_1x22_P2.54mm_Vertical","","1"
"J22","J2 switches (no ground) OUT - cable to the machine board","Connector_JST:JST_XH_B5B-XH-A_1x05_P2.50mm_Vertical","","1"
"J23","J3 NTC (the PID's sensor) OUT - cable to the machine board","Connector_JST:JST_XH_B2B-XH-A_1x02_P2.50mm_Vertical","","1"
"J24","J4 flow OUT - cable to the machine board","Connector_JST:JST_XH_B3B-XH-A_1x03_P2.50mm_Vertical","","1"
"J25","J5 display OUT - cable to the machine board","Connector_JST:JST_XH_B4B-XH-A_1x04_P2.50mm_Vertical","","1"
"JP1","(a1) 1Cup drive leg - OPEN in Phase 0","Connector_PinHeader_2.54mm:PinHeader_1x02_P2.54mm_Vertical","","1"
"JP2","(a2) 2Cup drive leg - OPEN in Phase 0","Connector_PinHeader_2.54mm:PinHeader_1x02_P2.54mm_Vertical","","1"
"JP3","(b) LED supply - OPEN until bench test","Connector_PinHeader_2.54mm:PinHeader_1x02_P2.54mm_Vertical","","1"
"JP4","selftest GPIO8-GPIO6 - NEVER fitted in service","Connector_PinHeader_2.54mm:PinHeader_1x02_P2.54mm_Vertical","","1"
"Q1-Q4","BC547B","Package_TO_SOT_THT:TO-92_Inline_Wide","","4"
"R1,R2,R8-R11","8.2k","Resistor_THT:R_Axial_DIN0207_L6.3mm_D2.5mm_P10.16mm_Horizontal","","6"
"R3","100k","Resistor_THT:R_Axial_DIN0207_L6.3mm_D2.5mm_P10.16mm_Horizontal","","1"
"R4-R7","150k","Resistor_THT:R_Axial_DIN0207_L6.3mm_D2.5mm_P7.62mm_Horizontal","","4"
"R12-R16","220k","Resistor_THT:R_Axial_DIN0207_L6.3mm_D2.5mm_P10.16mm_Horizontal","","5"
"R20-R26","10k","Resistor_THT:R_Axial_DIN0207_L6.3mm_D2.5mm_P2.54mm_Vertical","","7"
"R27-R30","330k","Resistor_THT:R_Axial_DIN0207_L6.3mm_D2.5mm_P2.54mm_Vertical","","4"
"R31","470k","Resistor_THT:R_Axial_DIN0207_L6.3mm_D2.5mm_P2.54mm_Vertical","","1"
"R32-R35","1k (value TBD)","Resistor_THT:R_Axial_DIN0207_L6.3mm_D2.5mm_P2.54mm_Vertical","","4"
"R36","1k (value TBD) - fit ONLY with U3","Resistor_THT:R_Axial_DIN0207_L6.3mm_D2.5mm_P2.54mm_Vertical","DNP","1"
"R40-R43","330 1%","Resistor_THT:R_Axial_DIN0207_L6.3mm_D2.5mm_P2.54mm_Vertical","","4"
"R44-R47","100k","Resistor_THT:R_Axial_DIN0207_L6.3mm_D2.5mm_P2.54mm_Vertical","","4"
"R48-R51","8.2k","Resistor_THT:R_Axial_DIN0207_L6.3mm_D2.5mm_P2.54mm_Vertical","","4"
"R60,R61","4.7M - DNP, fit ONE","Resistor_THT:R_Axial_DIN0207_L6.3mm_D2.5mm_P5.08mm_Vertical","DNP","2"
"R62","shunt - DNP, only if 5 V referenced","Resistor_THT:R_Axial_DIN0207_L6.3mm_D2.5mm_P2.54mm_Vertical","DNP","1"
"R63,R68","1k - DNP, fit ONE of R63/R68","Resistor_THT:R_Axial_DIN0207_L6.3mm_D2.5mm_P2.54mm_Vertical","DNP","2"
"R64","4.7M - DNP","Resistor_THT:R_Axial_DIN0207_L6.3mm_D2.5mm_P2.54mm_Vertical","DNP","1"
"R66","Rf - DNP: wire link = unity","Resistor_THT:R_Axial_DIN0207_L6.3mm_D2.5mm_P2.54mm_Vertical","DNP","1"
"R67","Rg - DNP, gain only","Resistor_THT:R_Axial_DIN0207_L6.3mm_D2.5mm_P2.54mm_Vertical","DNP","1"
"TP1","GND loop","TestPoint:TestPoint_Loop_D2.50mm_Drill1.0mm","","1"
"TP2","3V3 loop","TestPoint:TestPoint_Loop_D2.50mm_Drill1.0mm","","1"
"U1,U2","CD74HC221E","Package_DIP:DIP-16_W7.62mm_Socket","","2"
"U3","CD74HC221E - PROPOSED gate: socket fitted, chip OUT","Package_DIP:DIP-16_W7.62mm_Socket","","1"
"U4-U7","AQY212EH","Package_DIP:DIP-8_W7.62mm_Socket","","4"
"U8","MCP6002 - DNP","Package_DIP:DIP-8_W7.62mm","DNP","1"

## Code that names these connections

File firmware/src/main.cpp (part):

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// resistor dividers in the hundreds of kilohms, and the ESP32's internal
// resistors are ~45 kR — they would sit across the shunt leg and collapse the
// level. The display bus carries the same warning for the same arithmetic.
static constexpr uint8_t FLOW_PIN = 6;                      // J4 `#`, via 100K + 220K
// Order matches SwitchBank::Line, NOT J2's connector order (J2 runs
// +5V, Steam, 2Cup, 1Cup, Water — note 2Cup sits BEFORE 1Cup).
static constexpr uint8_t SW_PINS[SwitchBank::N_LINES] = { 7, 15, 16, 17 };
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// or duplicate an edge, and re-running this on a live tap is now a reachable
// case rather than a hypothetical one.
static void flowSetEnabled(bool on) {
  if (flow_on) detachInterrupt(digitalPinToInterrupt(FLOW_PIN));
  if (on) {
    pinMode(FLOW_PIN, INPUT);
    flow_head = flow_tail = 0;
    // Same rationale as switches.reset(): the taps go in one at a time, and
    // counts racked up by an earlier `flow on` against a floating pin describe
    // a tap that is no longer there. Without this the glitch warning below
    // latches on for ~16 shots, and `flow_ever` never lets status print
    // "NEVER" again — the one message that identifies a dead, freshly-refitted
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    flow_dropped = 0;
    flow_dropped_seen = 0;   // or a later drop count matching the old one goes unseen
    flow_ever = false;
    attachInterrupt(digitalPinToInterrupt(FLOW_PIN), flowIsr, FALLING);
  }
  flow_on = on;
}
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// `group` is the connector, which is where `pins` puts its " | " separators.
struct TapPin { const char* name; uint8_t pin; bool display; char group; };
static const TapPin TAP_PINS[] = {
  { "flow",  FLOW_PIN,         false, '4' },
  { "1cup",  SW_PINS[0],       false, '2' },
  { "2cup",  SW_PINS[1],       false, '2' },
  { "steam", SW_PINS[2],       false, '2' },
  { "water", SW_PINS[3],       false, '2' },
  { "clk",   DISPLAY_CLK_PIN,  true,  '5' },
  { "data",  DISPLAY_DATA_PIN, true,  '5' },
};
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  { "2Cup photoMOS 1", 40, 47 },    // U1 ch2: pin 9 A̅, pin 5 Q
  { "2Cup photoMOS 2", 39, 21 },    // U2 ch2: pin 9 A̅, pin 5 Q
};
static constexpr uint8_t GATE_EN_PIN   = 38;   // U3 R̅, 10 K pull-down
static constexpr uint8_t GATE_TRIG_PIN = 10;   // U3 A̅, 10 K pull-up
static constexpr uint8_t GATE_Q_PIN    = 9;    // U3 Q (the tied R̅ net), via 1 K
// The run's hard cap: past this GPIO38 drops whatever Q is doing. Above
// the gate's 500 ms worst-corner cap, so a held gate shows as HELD rather
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// chip or 1 K is out, and then can trip the idle check at random instead of
// showing NO PULSE.
static void driveRelease(int no_pd_pin = -1) {
  digitalWrite(GATE_EN_PIN, LOW);
  pinMode(GATE_EN_PIN, INPUT);
  pinMode(GATE_TRIG_PIN, INPUT);
  pinMode(GATE_Q_PIN, INPUT_PULLDOWN);
  for (const DriveChan& c : DRIVE_CH) {
    pinMode(c.trig, INPUT);
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
  if (sub == "" || sub == "status") {
    out.printf("# drive pins (nothing driven): GPIO38 en=%d  gate A̅=%d Q=%d\n",
               digitalRead(GATE_EN_PIN), digitalRead(GATE_TRIG_PIN), digitalRead(GATE_Q_PIN));
    for (int i = 0; i < 4; i++)
      out.printf("#   ch%d %-16s A̅(GPIO%u)=%d  Q(GPIO%u)=%d\n", i + 1, DRIVE_CH[i].name,
                 DRIVE_CH[i].trig, digitalRead(DRIVE_CH[i].trig), DRIVE_CH[i].q, digitalRead(DRIVE_CH[i].q));
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    delayMicroseconds(100);   // let the pulls settle the just-released pins
    // Every A̅ an armed R̅ rise could fire must read HIGH, and every Q LOW,
    // first (docs/phase-0-plan.md: never let R̅ rise without reading them).
    bool idle = digitalRead(GATE_TRIG_PIN) == HIGH && digitalRead(GATE_EN_PIN) == LOW
             && digitalRead(GATE_Q_PIN) == LOW;
    for (const DriveChan& c : DRIVE_CH)
      idle = idle && digitalRead(c.trig) == HIGH && digitalRead(c.q) == LOW;
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    QTrace q[4], gate;
    bool held;
    int64_t t0;
    // Arm: GPIO38 high. With the gate fitted that only enables it (its A̅ is
    // high, so the R̅ rise is inert); in the no-gate rework (`direct`) it
    // drives the tied R̅ net and arms the four drive channels.
    digitalWrite(GATE_EN_PIN, HIGH);
    pinMode(GATE_EN_PIN, OUTPUT);
    delayMicroseconds(50);
    if (gate_only) {
      t0 = esp_timer_get_time();
      drivePulseLow(GATE_TRIG_PIN);
      held = driveSample(t0, q, gate, -1);
    } else {
      if (fire) {
        drivePulseLow(GATE_TRIG_PIN);
        int64_t g0 = esp_timer_get_time();
        while (!digitalRead(GATE_Q_PIN) && esp_timer_get_time() - g0 < 1000) {}
        if (!digitalRead(GATE_Q_PIN)) {
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    Serial.printf("# display bus %s (clk=GPIO%u data=GPIO%u)\n",
                  on ? "on" : "off (see 'display on')",
                  DISPLAY_CLK_PIN, DISPLAY_DATA_PIN);
    Serial.printf("# flow %s (GPIO%u) | switches %s (1cup=GPIO%u 2cup=GPIO%u steam=GPIO%u water=GPIO%u)\n",
                  fl ? "on" : "off", FLOW_PIN, sw ? "on" : "off",
                  SW_PINS[0], SW_PINS[1], SW_PINS[2], SW_PINS[3]);
  }

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
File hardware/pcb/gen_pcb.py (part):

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# left, rows staggered so no two raw pads are neighbours
at("R2", 16.0, 23.5, 180)          # ESD4: raw 16,23.5   -> sense 5.84
at("R1", 13.5, 26.7, 180)          # ESD1: raw 13.5,26.7 -> sense 3.34
# FLOW: raw pad under J4 pin 1, which is # (S.J4_FLOW_PIN, asserted in finish.py)
at("R3", 31.5, 25.5, 180)          # raw 31.5,25.5 -> sense 21.34
# --- sense shunts and candidate caps, flat, under the devkit
for i, ref in enumerate(["R8", "R9", "R10", "R11", "R12", "R13", "R14",
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# --- MACHINE CORNER. J2's 150 K lie flat, raw pad (pad 1) on the right
# two columns away from the next lever's fan, so that no fan passes another
# lever's raw pad closer than 2 mm (pre-order review S5): Water's pad sits
# 3 mm LEFT of its pin, 2Cup's 1.5 mm RIGHT of its pin, and Steam's fan runs
# down a lane at x 82.6 to stay clear of 2Cup's pad.
# 2Cup's row is ABOVE 1Cup's: the 2Cup return comes from the outer lane
# (x 98.6), so it has to turn in above the top of the 1Cup lane (x 94.7).
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    upright(c["rb1"], COL2_X, y0 + 4.54, "up")       # readback on top, Q below
at("C15", 54.5, 24.5)                      # U1 decoupling, by pin 16
# --- J3 NTC tap, all DNP. The two raw-side 4.7 M stand upright with their
# raw pad under the OUT pins and their far pad (NTC_MID) pointing AWAY from
# each other; everything from NTC_MID on is behind 4.7 M and is ours.
upright("R60", 44.0, 23.4, "right")        # P1 raw -> mid at 49.08
upright("R61", 40.5, 23.4, "left")         # P2 raw -> mid at 35.42
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        # fans from the OUT pins straight down to the raw pads of the taps
        ("ESD4_RAW", F_, [("J25", "2"), ("R2", "1")]),
        ("ESD1_RAW", F_, [("J25", "3"), ("R1", "1")]),
        ("FLOW_RAW", F_, [("J24", S.J4_FLOW_PIN), ("R3", "1")]),
        ("NTC_P1_RAW", F_, [("J23", "1"), ("R60", "1")]),
        ("NTC_P2_RAW", F_, [("J23", "2"), (41.5, 21.0), (40.5, 22.0),
                            ("R61", "1")]),
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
